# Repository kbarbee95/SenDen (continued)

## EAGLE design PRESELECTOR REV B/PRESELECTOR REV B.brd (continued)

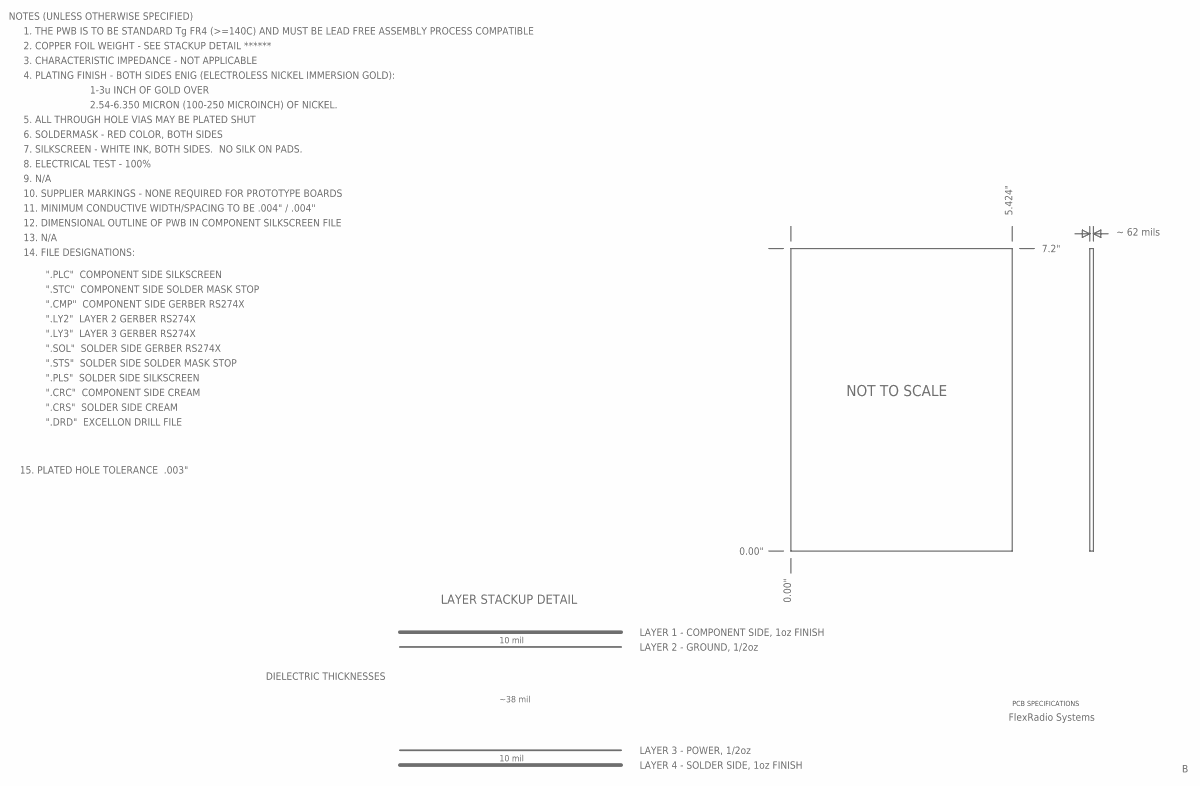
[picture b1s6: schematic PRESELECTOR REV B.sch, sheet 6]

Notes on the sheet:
NOTES (UNLESS OTHERWISE SPECIFIED)
1. THE PWB IS TO BE STANDARD Tg FR4 (>=140C) AND MUST BE LEAD FREE ASSEMBLY PROCESS COMPATIBLE
2. COPPER FOIL WEIGHT - SEE STACKUP DETAIL ******
3. CHARACTERISTIC IMPEDANCE - NOT APPLICABLE
4. PLATING FINISH - BOTH SIDES ENIG (ELECTROLESS NICKEL IMMERSION GOLD):
1-3u INCH OF GOLD OVER
2.54-6.350 MICRON (100-250 MICROINCH) OF NICKEL.
5. ALL THROUGH HOLE VIAS MAY BE PLATED SHUT
6. SOLDERMASK - RED COLOR, BOTH SIDES
7. SILKSCREEN - WHITE INK, BOTH SIDES. NO SILK ON PADS.
8. ELECTRICAL TEST - 100%
9. N/A
10. SUPPLIER MARKINGS - NONE REQUIRED FOR PROTOTYPE BOARDS
11. MINIMUM CONDUCTIVE WIDTH/SPACING TO BE .004" / .004"
12. DIMENSIONAL OUTLINE OF PWB IN COMPONENT SILKSCREEN FILE
7.2"
5.424"
14. FILE DESIGNATIONS:
".CMP" COMPONENT SIDE GERBER RS274X
".LY2" LAYER 2 GERBER RS274X
".LY3" LAYER 3 GERBER RS274X
".SOL" SOLDER SIDE GERBER RS274X
".PLC" COMPONENT SIDE SILKSCREEN
".PLS" SOLDER SIDE SILKSCREEN
".CRC" COMPONENT SIDE CREAM
".CRS" SOLDER SIDE CREAM
".STC" COMPONENT SIDE SOLDER MASK STOP
".STS" SOLDER SIDE SOLDER MASK STOP
".DRD" EXCELLON DRILL FILE
LAYER 1 - COMPONENT SIDE, 1oz FINISH
LAYER 2 - GROUND, 1/2oz
LAYER 3 - POWER, 1/2oz
LAYER 4 - SOLDER SIDE, 1oz FINISH
~ 62 mils
DIELECTRIC THICKNESSES
10 mil
~38 mil
LAYER STACKUP DETAIL
15. PLATED HOLE TOLERANCE .003"
NOT TO SCALE

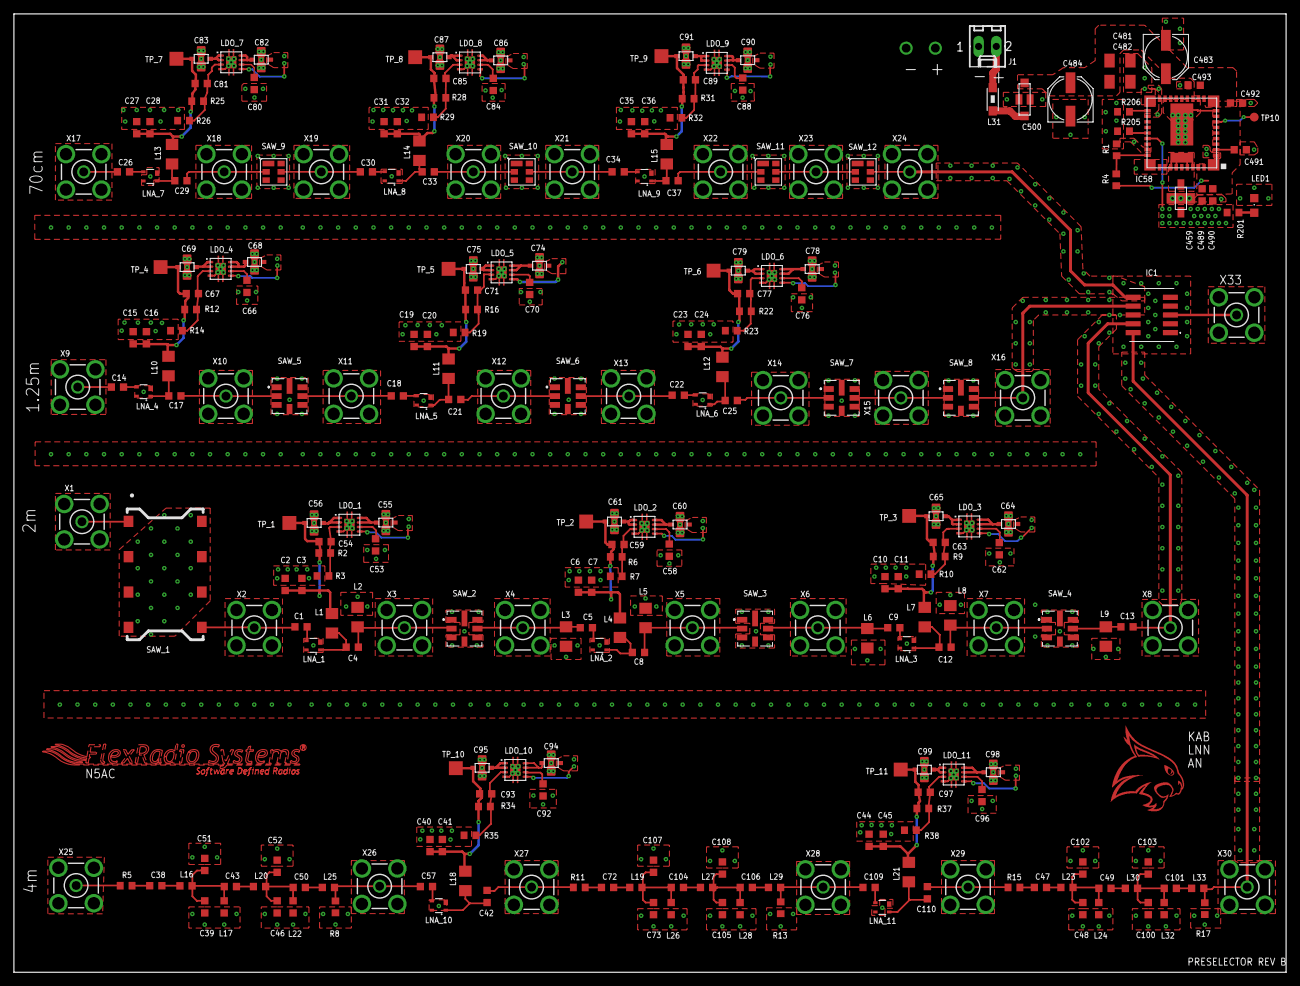
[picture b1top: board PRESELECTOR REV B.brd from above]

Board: 4 copper layers, 182.9 x 137.8 mm, 268 parts (0 on the bottom side), 139 nets.

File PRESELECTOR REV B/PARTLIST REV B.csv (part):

"Part";"Value";"Device";"Package";"Description";"";
"C1";"100p";"C-USC0603K";"C0603K";"CAPACITOR, American symbol";"";
"C2";"0.1u";"C-USC0603K";"C0603K";"CAPACITOR, American symbol";"";
"C3";"100p";"C-USC0603K";"C0603K";"CAPACITOR, American symbol";"";
"C4";"8p";"C-USC0603K";"C0603K";"CAPACITOR, American symbol";"";
"C5";"12p";"C-USC0603K";"C0603K";"CAPACITOR, American symbol";"";
"C6";"0.1u";"C-USC0603K";"C0603K";"CAPACITOR, American symbol";"";
"C7";"100p";"C-USC0603K";"C0603K";"CAPACITOR, American symbol";"";
"C8";"8p";"C-USC0603K";"C0603K";"CAPACITOR, American symbol";"";
"C9";"12p";"C-USC0603K";"C0603K";"CAPACITOR, American symbol";"";
"C10";"0.1u";"C-USC0603K";"C0603K";"CAPACITOR, American symbol";"";
"C11";"100p";"C-USC0603K";"C0603K";"CAPACITOR, American symbol";"";
"C12";"8p";"C-USC0603K";"C0603K";"CAPACITOR, American symbol";"";
"C13";"12p";"C-USC0603K";"C0603K";"CAPACITOR, American symbol";"";
"C14";"100p";"C-USC0603K";"C0603K";"CAPACITOR, American symbol";"";
"C15";"0.1u";"C-USC0603K";"C0603K";"CAPACITOR, American symbol";"";
"C16";"100p";"C-USC0603K";"C0603K";"CAPACITOR, American symbol";"";
"C17";"100p";"C-USC0603K";"C0603K";"CAPACITOR, American symbol";"";
"C18";"100p";"C-USC0603K";"C0603K";"CAPACITOR, American symbol";"";
"C19";"0.1u";"C-USC0603K";"C0603K";"CAPACITOR, American symbol";"";
"C20";"100p";"C-USC0603K";"C0603K";"CAPACITOR, American symbol";"";
"C21";"100p";"C-USC0603K";"C0603K";"CAPACITOR, American symbol";"";
"C22";"100p";"C-USC0603K";"C0603K";"CAPACITOR, American symbol";"";
"C23";"0.1u";"C-USC0603K";"C0603K";"CAPACITOR, American symbol";"";
"C24";"100p";"C-USC0603K";"C0603K";"CAPACITOR, American symbol";"";
"C25";"100p";"C-USC0603K";"C0603K";"CAPACITOR, American symbol";"";
"C26";"100p";"C-USC0603K";"C0603K";"CAPACITOR, American symbol";"";
"C27";"0.1u";"C-USC0603K";"C0603K";"CAPACITOR, American symbol";"";
"C28";"100p";"C-USC0603K";"C0603K";"CAPACITOR, American symbol";"";
"C29";"100p";"C-USC0603K";"C0603K";"CAPACITOR, American symbol";"";
"C30";"100p";"C-USC0603K";"C0603K";"CAPACITOR, American symbol";"";
"C31";"0.1u";"C-USC0603K";"C0603K";"CAPACITOR, American symbol";"";
"C32";"100p";"C-USC0603K";"C0603K";"CAPACITOR, American symbol";"";
"C33";"100p";"C-USC0603K";"C0603K";"CAPACITOR, American symbol";"";
"C34";"100p";"C-USC0603K";"C0603K";"CAPACITOR, American symbol";"";
"C35";"0.1u";"C-USC0603K";"C0603K";"CAPACITOR, American symbol";"";
"C36";"100p";"C-USC0603K";"C0603K";"CAPACITOR, American symbol";"";
"C37";"100p";"C-USC0603K";"C0603K";"CAPACITOR, American symbol";"";
"C38";"4.2p";"C-USC0603K";"C0603K";"CAPACITOR, American symbol";"";
"C39";"650p";"C-USC0603K";"C0603K";"CAPACITOR, American symbol";"";
"C40";"0.1u";"C-USC0603K";"C0603K";"CAPACITOR, American symbol";"";
"C41";"100p";"C-USC0603K";"C0603K";"CAPACITOR, American symbol";"";
"C42";"100p";"C-USC0603K";"C0603K";"CAPACITOR, American symbol";"";
"C43";"1.3p";"C-USC0603K";"C0603K";"CAPACITOR, American symbol";"";
"C44";"0.1u";"C-USC0603K";"C0603K";"CAPACITOR, American symbol";"";
"C45";"100p";"C-USC0603K";"C0603K";"CAPACITOR, American symbol";"";
"C46";"650p";"C-USC0603K";"C0603K";"CAPACITOR, American symbol";"";
"C47";"4.2p";"C-USC0603K";"C0603K";"CAPACITOR, American symbol";"";
"C48";"650p";"C-USC0603K";"C0603K";"CAPACITOR, American symbol";"";
"C49";"1.3p";"C-USC0603K";"C0603K";"CAPACITOR, American symbol";"";
"C50";"4.2p";"C-USC0603K";"C0603K";"CAPACITOR, American symbol";"";
"C51";"650p";"C-USC0603K";"C0603K";"CAPACITOR, American symbol";"";
"C52";"650p";"C-USC0603K";"C0603K";"CAPACITOR, American symbol";"";
"C53";"470n";"C-USC0603K";"C0603K";"CAPACITOR, American symbol";"";
"C54";"470n";"C-USC0603K";"C0603K";"CAPACITOR, American symbol";"";
"C55";"NFM21PS106B0J3D";"NFM21PS";"NFM21PS";"";"";
"C56";"NFM21PS106B0J3D";"NFM21PS";"NFM21PS";"";"";
"C57";"100p";"C-USC0603K";"C0603K";"CAPACITOR, American symbol";"";
"C58";"470n";"C-USC0603K";"C0603K";"CAPACITOR, American symbol";"";
"C59";"470n";"C-USC0603K";"C0603K";"CAPACITOR, American symbol";"";
"C60";"NFM21PS106B0J3D";"NFM21PS";"NFM21PS";"";"";
"C61";"NFM21PS106B0J3D";"NFM21PS";"NFM21PS";"";"";
"C62";"470n";"C-USC0603K";"C0603K";"CAPACITOR, American symbol";"";
"C63";"470n";"C-USC0603K";"C0603K";"CAPACITOR, American symbol";"";
"C64";"NFM21PS106B0J3D";"NFM21PS";"NFM21PS";"";"";
"C65";"NFM21PS106B0J3D";"NFM21PS";"NFM21PS";"";"";
"C66";"470n";"C-USC0603K";"C0603K";"CAPACITOR, American symbol";"";
"C67";"470n";"C-USC0603K";"C0603K";"CAPACITOR, American symbol";"";
"C68";"NFM21PS106B0J3D";"NFM21PS";"NFM21PS";"";"";
"C69";"NFM21PS106B0J3D";"NFM21PS";"NFM21PS";"";"";
"C70";"470n";"C-USC0603K";"C0603K";"CAPACITOR, American symbol";"";
"C71";"470n";"C-USC0603K";"C0603K";"CAPACITOR, American symbol";"";
"C72";"4.2p";"C-USC0603K";"C0603K";"CAPACITOR, American symbol";"";
"C73";"650p";"C-USC0603K";"C0603K";"CAPACITOR, American symbol";"";
"C74";"NFM21PS106B0J3D";"NFM21PS";"NFM21PS";"";"";
"C75";"NFM21PS106B0J3D";"NFM21PS";"NFM21PS";"";"";
"C76";"470n";"C-USC0603K";"C0603K";"CAPACITOR, American symbol";"";
"C77";"470n";"C-USC0603K";"C0603K";"CAPACITOR, American symbol";"";
"C78";"NFM21PS106B0J3D";"NFM21PS";"NFM21PS";"";"";
"C79";"NFM21PS106B0J3D";"NFM21PS";"NFM21PS";"";"";
"C80";"470n";"C-USC0603K";"C0603K";"CAPACITOR, American symbol";"";
"C81";"470n";"C-USC0603K";"C0603K";"CAPACITOR, American symbol";"";
"C82";"NFM21PS106B0J3D";"NFM21PS";"NFM21PS";"";"";
"C83";"NFM21PS106B0J3D";"NFM21PS";"NFM21PS";"";"";
"C84";"470n";"C-USC0603K";"C0603K";"CAPACITOR, American symbol";"";
"C85";"470n";"C-USC0603K";"C0603K";"CAPACITOR, American symbol";"";
"C86";"NFM21PS106B0J3D";"NFM21PS";"NFM21PS";"";"";
"C87";"NFM21PS106B0J3D";"NFM21PS";"NFM21PS";"";"";
"C88";"470n";"C-USC0603K";"C0603K";"CAPACITOR, American symbol";"";
"C89";"470n";"C-USC0603K";"C0603K";"CAPACITOR, American symbol";"";
"C90";"NFM21PS106B0J3D";"NFM21PS";"NFM21PS";"";"";
"C91";"NFM21PS106B0J3D";"NFM21PS";"NFM21PS";"";"";
"C92";"470n";"C-USC0603K";"C0603K";"CAPACITOR, American symbol";"";
"C93";"470n";"C-USC0603K";"C0603K";"CAPACITOR, American symbol";"";
"C94";"NFM21PS106B0J3D";"NFM21PS";"NFM21PS";"";"";
"C95";"NFM21PS106B0J3D";"NFM21PS";"NFM21PS";"";"";
"C96";"470n";"C-USC0603K";"C0603K";"CAPACITOR, American symbol";"";
"C97";"470n";"C-USC0603K";"C0603K";"CAPACITOR, American symbol";"";
"C98";"NFM21PS106B0J3D";"NFM21PS";"NFM21PS";"";"";
"C99";"NFM21PS106B0J3D";"NFM21PS";"NFM21PS";"";"";
"C100";"650p";"C-USC0603K";"C0603K";"CAPACITOR, American symbol";"";
"C101";"4.2p";"C-USC0603K";"C0603K";"CAPACITOR, American symbol";"";
"C102";"650p";"C-USC0603K";"C0603K";"CAPACITOR, American symbol";"";
"C103";"650p";"C-USC0603K";"C0603K";"CAPACITOR, American symbol";"";
"C104";"1.3p";"C-USC0603K";"C0603K";"CAPACITOR, American symbol";"";
"C105";"650p";"C-USC0603K";"C0603K";"CAPACITOR, American symbol";"";
"C106";"4.2p";"C-USC0603K";"C0603K";"CAPACITOR, American symbol";"";
"C107";"650p";"C-USC0603K";"C0603K";"CAPACITOR, American symbol";"";
"C108";"650p";"C-USC0603K";"C0603K";"CAPACITOR, American symbol";"";
"C109";"100p";"C-USC0603K";"C0603K";"CAPACITOR, American symbol";"";
"C110";"100p";"C-USC0603K";"C0603K";"CAPACITOR, American symbol";"";
"C459";"";"NFM31PC276B0J3L";"NFM31PC276";"";"";
"C481";"33u";"C-USC1206K";"C1206K";"CAPACITOR, American symbol";"";
"C482";"33u";"C-USC1206K";"C1206K";"CAPACITOR, American symbol";"";
"C483";"EEE-FK1V470P";"CPOL-USD";"PANASONIC_D";"POLARIZED CAPACITOR, American symbol";"";
"C484";"EEE-FK1V470P";"CPOL-USD";"PANASONIC_D";"POLARIZED CAPACITOR, American symbol";"";
"C489";".1u 50V";"C-USC0603K";"C0603K";"CAPACITOR, American symbol";"";
"C490";".1u 50V";"C-USC0603K";"C0603K";"CAPACITOR, American symbol";"";
"C491";".1u 50V";"C-USC0603K";"C0603K";"CAPACITOR, American symbol";"";
"C492";".1u 50V";"C-USC0603K";"C0603K";"CAPACITOR, American symbol";"";
"C493";".1u 50V";"C-USC0603K";"C0603K";"CAPACITOR, American symbol";"";
"C500";"NFM41PC155B1E3";"NFM41PC155B1E3";"NFM1806";"Murata Feed Through Capacitor 1806 SMD";"";
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
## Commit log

2019-09-04 Added Git Cheatsheet
2019-09-04 Added Preselector.sch & SeniorDesign.lbr
2019-09-04 Test Merging of Files
2019-09-04 Test merging of freaking files
2019-09-04 Overwriting primary with back-up due to error
2019-09-05 Finished the 1.25m. Double check if you'd like.
2019-09-05 Kenneth, please check the 70cm because i think i f*ked up, jk teehee
2019-09-05 2m band is revised. Double check if you'd like, Kenneth.
2019-09-06 Made minor changes to schematic
2019-09-09 Saved Preselector to backup
2019-09-09 Cleaned up schematic and began board design
2019-09-09 Created board, edited senior design lib, added .gitignore file
2019-09-11 Ken, I renamed the capacitors and inductors in order as they appear on each Filter and LNA respectively. If you see anything wrong let me know.
2019-09-11 Deleted .brd to sync schematic for annotation
2019-09-11 Created board and did the 2m layout.
2019-09-12 1.25M band added to PCB design
2019-09-12 kenneth, 70cm band is added to pcb
2019-09-12 Figured out how to GND polygons and started doing that.
2019-09-12 Fixed s511215 device in library, added 4m to schematic and finished 4m on the board.
2019-09-12 Added Band markers on the board
2019-09-12 Fixed the suggestion from albert of the rf input connected to ground
2019-09-12 Kenneth, I redid the 1.25m and 2m band, replaced the wire with the route. The 4m band, I put the capacitors 44 and 45 in order, originally they were in 45 then 44 order. Other than that, the board se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
2019-09-14 Renamed 4m net, look at the naming convention on there to continue. I also renamed the beginning of the 2m band, I'm renaming the 5v3 net to just +5v. I think the voltage can be the same name because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
2019-09-16 Added connectors on 4m band and also copied LDO over
2019-09-16 Connected the connectors (schematic). Ripped up traces from board.
2019-09-17 Aligned most rows. Added some vias and fixed the divider polygon that can be copied for other bands.
2019-09-17 started fixing some of the ERC errors in the schematic. DRC is for the board. Cut down on half of the errors and approved a few that were from the POWER SYSTEM page.
2019-09-17 Fixed all ERC errors
2019-09-17 Routed all signal wires, left notes on the board for you. Next we need to add an LDO to each amplifier on the schematic. Will be quite a bit of work. All traces on the schematic have been renamed pro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
2019-09-17 Added power plane polygon. Read last commit for important notes.
2019-09-18 Added first 2 LDO's on 2m band
2019-09-18 I think i did it correctly.
2019-09-18 Added LDO's to schematic, will add to board shortly.
2019-09-19 hi kenneth, just pushing the files that I worked on in class
2019-09-19 Approved 313 DRC errors for the LDO via spacing and pad-via spacing.
2019-09-20 Oriented a few more LDO's and placed one on the board to see what it looked like.
2019-09-21 Finished modeling the LDO configurations
2019-09-22 Hey, Kenneth, I added the LDO's and routed the ones on the 2m band, let me know if that looks right so I can continue working on it as is. Thanks.
2019-09-22 Just remodeled the chains, miscellaneous stuff.
2019-09-23 Routed LDO's, changed widths of the routes as well, grounded some vias as well. Let me know if everything looks okay.
2019-09-27 Started laying out voltage regulator.
2019-09-27 Added the SCA-4-10+ component onto SeniorDesign.lbr
2019-09-29 just removed the unneccessary stuff from the value discripton on the capacitors and inductors.
2019-09-29 Finished wiring Voltage Reg. Please double check all the connections.
2019-09-30 Just connected a route from L31 to C500 on the power regulator n the pcb layout.
2019-09-30 Finished connecting power supply
2019-09-30 Need 2 polygons for +5v3
2019-09-30 Fixed Volt Reg power supply and moves Volt Reg names.
2019-09-30 routed some stuff, added +5V3 polygons.
2019-10-01 All components should be connected to ground as well as all pre_pwr wires have been routed. 4 air wires remain...
2019-10-02 Found 1 airwire, 3 left.
2019-10-02 Finished board, 0 airwires left. Check for polygon shorts.
2019-10-02 Corrected some DRC errors.
2019-10-03 Board is ready for review.
2019-10-04 Minor changes that steve made during the meeting, still needs all the changes suggested.
2019-10-05 Changes we made at my house.
2019-10-06 rerouted rf traces, deleted polygons and vias. still need to figure out resistor values for power supply.
2019-10-07 Only need to change voltage reg resistor
2019-10-07 deleted mosfet from sch, added resistors onto the schematic power supply UVLO, routed new components in pcb layout, onto the power regulator
2019-10-09 New files from Steve with logo.
2019-10-09 added logos, initials
2019-10-09 checked drc's, checked them out
2019-10-09 Changed position of pin 1 locator
2019-10-14 Changed all components from 0402 to 0603 and corrected a few DRC's
2019-10-14 Corrected some DRC errors
2019-10-14 drc'ed what remained
2019-10-15 Created Gerbers, fixed some traces, and moved names around.
2019-10-19 Created copies of .brd and .sch for REV A
2019-10-20 Reworked board, created new filter and made gerbers for REV B. Sent gerbers to steve
2019-10-22 Crated gerbers for REV B, FINAL CONFIG for production
2019-10-25 Added 70 MHz ELSIE Filter design.
2019-11-22 Added 70MHz filter file for Elsie
